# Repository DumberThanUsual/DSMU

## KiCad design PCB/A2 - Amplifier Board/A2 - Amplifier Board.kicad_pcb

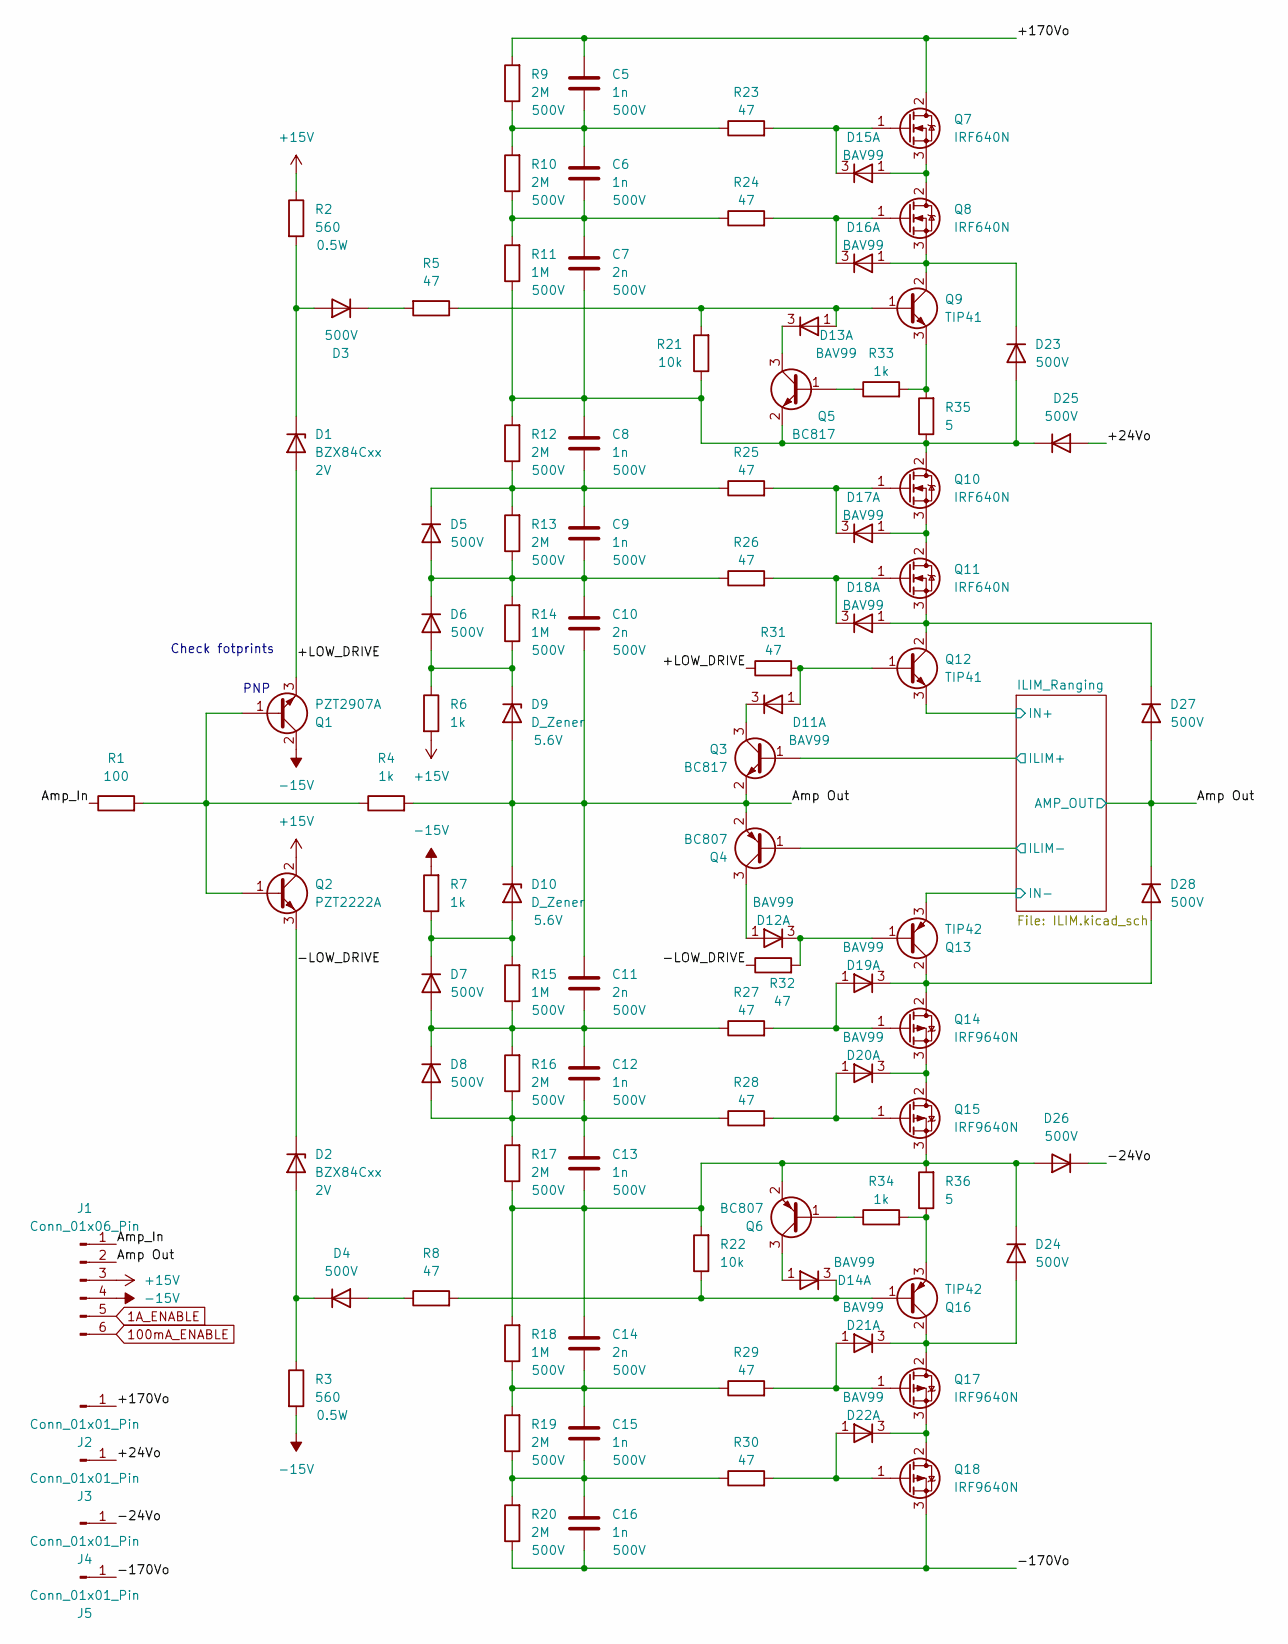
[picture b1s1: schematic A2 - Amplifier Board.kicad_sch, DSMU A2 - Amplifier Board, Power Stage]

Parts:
C5, C6, C8, C9, C12, C13, C15, C16: 1n; C_1206_3216Metric; Voltage Rating 500V
C7, C10, C11, C14: 2n; C_1206_3216Metric; Voltage Rating 500V
D1, D2: BZX84Cxx; SOT-23; Zener Voltage 2V
D3, D4, D5, D6, D7, D8, D23, D24, D25, D26, D27, D28: STTH1R06A; D_SMA; Volatage Rating 500V
D9, D10: D_Zener; D_SOD-123; Zener Voltage 5.6V
D11, D12, D13, D14, D15, D16, D17, D18, D19, D20, D21, D22: BAV99; SOT-23-3
J1: Conn_01x06_Pin; PinHeader_1x06_P2.54mm_Vertical
J2, J3, J4, J5: Conn_01x01_Pin; PinHeader_1x01_P2.54mm_Vertical
Q1: PZT2907A; SOT-223-3_TabPin2
Q2: PZT2222A; SOT-223-3_TabPin2
Q3, Q5: BC817; SOT-23
Q4, Q6: BC807; SOT-23
Q7, Q8, Q10, Q11: IRF640N; TO-220-3_Vertical
Q9, Q12: TIP41; TO-220-3_Vertical
Q13, Q16: TIP42; TO-220-3_Vertical
Q14, Q15, Q17, Q18: IRF9640N; TO-220-3_Vertical
R1: 100; R_0603_1608Metric
R2, R3: 560; R_1206_3216Metric; Power Rating 0.5W
R4, R6, R7, R33, R34: 1k; R_0603_1608Metric
R5, R8, R23, R24, R25, R26, R27, R28, R29, R30, R31, R32: 47; R_0603_1608Metric
R9, R10, R12, R13, R16, R17, R19, R20: 2M; R_1206_3216Metric; Voltage Rating 500V
R11, R14, R15, R18: 1M; R_1206_3216Metric; Voltage Rating 500V
R21, R22: 10k; R_0603_1608Metric
R35, R36: 5; R_0603_1608Metric

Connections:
1A_ENABLE: J1.5; also elsewhere on the board
100mA_ENABLE: J1.6; also elsewhere on the board
/+24Vo: D25.2 (A), J3.1
/+170Vo: C5.1, J2.1, Q7.2 (D), R9.2
/+LOW_DRIVE: D1.1 (A), Q1.3 (E), R31.1
/-24Vo: D26.1 (K), J4.1
/-170Vo: C16.2, J5.1, Q18.3 (S), R20.1
/-LOW_DRIVE: D2.3 (K), Q2.3 (E), R32.1
/Amp Out: C10.2, C11.1, D9.2 (A), D10.1 (K), D27.2 (A), D28.1 (K), J1.2, Q3.2 (E), Q4.2 (E), R4.2; also elsewhere on the board
/Amp_In: J1.1, R1.1
/ILIM_Ranging/ILIM+: Q3.1 (B); also elsewhere on the board
/ILIM_Ranging/ILIM-: Q4.1 (B); also elsewhere on the board
/ILIM_Ranging/IN+: Q12.3 (E); also elsewhere on the board
/ILIM_Ranging/IN-: Q13.3 (E); also elsewhere on the board
unnamed: C5.2, C6.1, R9.1, R10.2, R23.1
unnamed: C6.2, C7.1, R10.1, R11.2, R24.1
unnamed: C14.2, C15.1, R18.1, R19.2, R29.1
unnamed: C15.2, C16.1, R19.1, R20.2, R30.1
unnamed: D1.3 (K), D3.2 (A), R2.2
unnamed: D2.1 (A), D4.1 (K), R3.1
unnamed: D3.1 (K), R5.2
unnamed: D4.2 (A), R8.1
unnamed: C9.2, C10.1, D5.2 (A), D6.1 (K), R13.1, R14.2, R26.1
unnamed: C8.2, C9.1, D5.1 (K), R12.1, R13.2, R25.1
unnamed: D6.2 (A), D9.1 (K), R6.1, R14.1
unnamed: C11.2, C12.1, D7.2 (A), D8.1 (K), R15.1, R16.2, R27.1
unnamed: C12.2, C13.1, D8.2 (A), R16.1, R17.2, R28.1
unnamed: D7.1 (K), D10.2 (A), R7.1, R15.2
unnamed: D11.1 (A), Q12.1 (B), R31.2
unnamed: D11.3 (K), Q3.3 (C)
unnamed: D12.1 (A), Q4.3 (C)
unnamed: D12.3 (K), Q13.1 (B), R32.2
unnamed: D13.1 (A), Q9.1 (B), R5.1, R21.2
unnamed: D13.3 (K), Q5.3 (C)
unnamed: D14.1 (A), Q6.3 (C)
unnamed: D14.3 (K), Q16.1 (B), R8.2, R22.1
unnamed: D15.1 (A), Q7.3 (S), Q8.2 (D)
unnamed: D15.3 (K), Q7.1 (G), R23.2
unnamed: D16.1 (A), D23.1 (K), Q8.3 (S), Q9.2 (C)
unnamed: D16.3 (K), Q8.1 (G), R24.2
unnamed: D17.1 (A), Q10.3 (S), Q11.2 (D)
unnamed: D17.3 (K), Q10.1 (G), R25.2
unnamed: D18.1 (A), D27.1 (K), Q11.3 (S), Q12.2 (C)
unnamed: D18.3 (K), Q11.1 (G), R26.2
unnamed: D19.1 (A), Q14.1 (G), R27.2
unnamed: D19.3 (K), D28.2 (A), Q13.2 (C), Q14.2 (D)
unnamed: D20.1 (A), Q15.1 (G), R28.2
unnamed: D20.3 (K), Q14.3 (S), Q15.2 (D)
unnamed: D21.1 (A), Q17.1 (G), R29.2
unnamed: D21.3 (K), D24.2 (A), Q16.2 (C), Q17.2 (D)
unnamed: D22.1 (A), Q18.1 (G), R30.2
unnamed: D22.3 (K), Q17.3 (S), Q18.2 (D)
unnamed: C7.2, C8.1, D23.2 (A), D25.1 (K), Q5.2 (E), Q10.2 (D), R11.1, R12.2, R21.1, R35.1
unnamed: C13.2, C14.1, D24.1 (K), D26.2 (A), Q6.2 (E), Q15.3 (S), R17.1, R18.2, R22.2, R36.2
unnamed: Q5.1 (B), R33.1
unnamed: Q6.1 (B), R34.1
unnamed: Q9.3 (E), R33.2, R35.2
unnamed: Q16.3 (E), R34.2, R36.1

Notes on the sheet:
PNP
Check fotprints

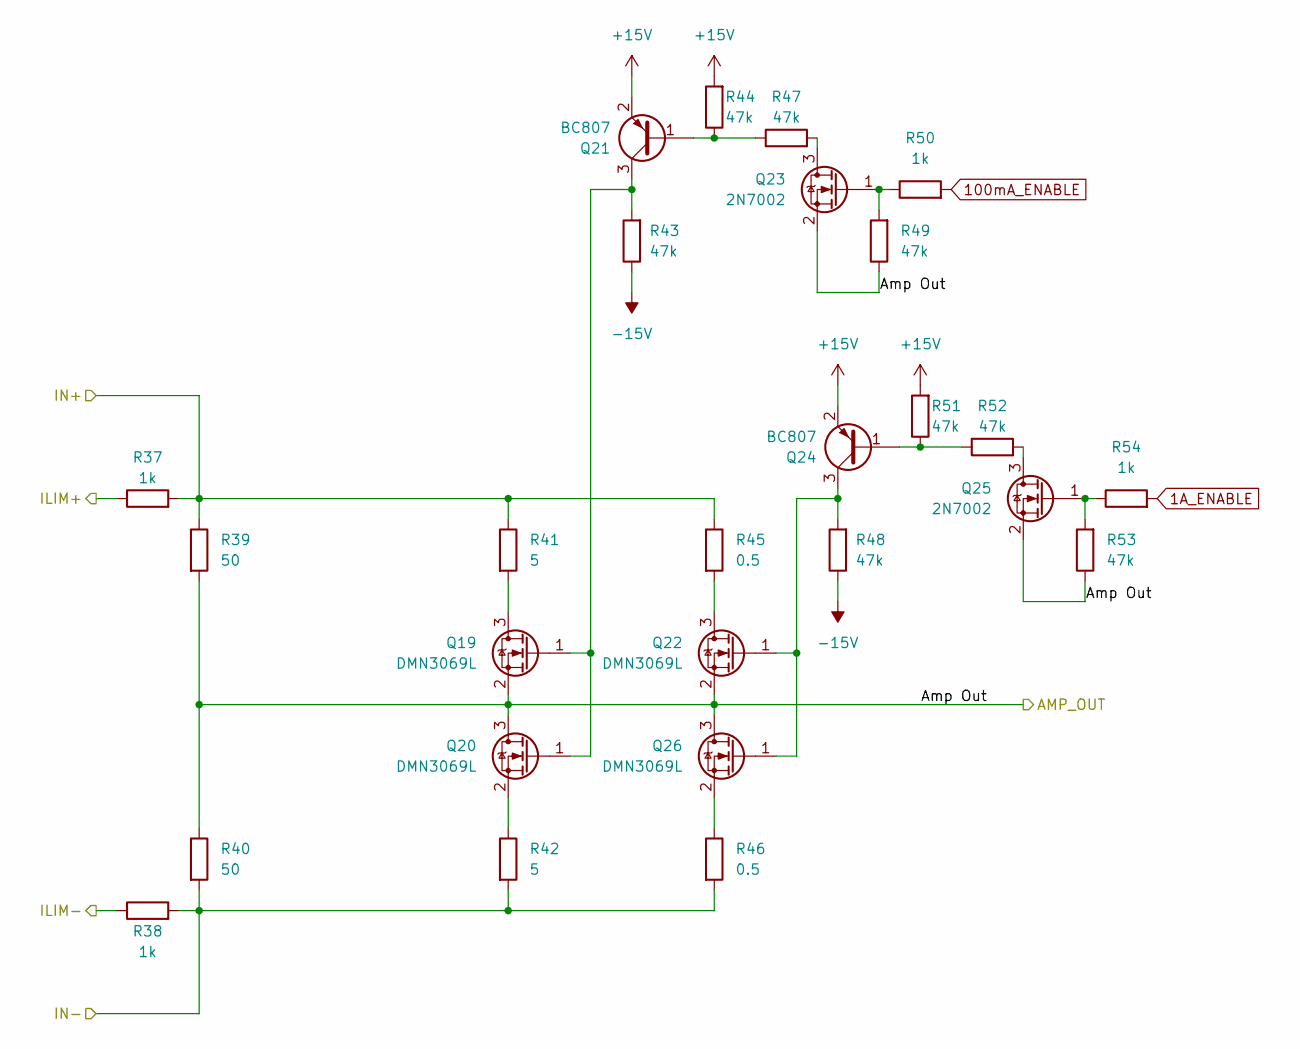
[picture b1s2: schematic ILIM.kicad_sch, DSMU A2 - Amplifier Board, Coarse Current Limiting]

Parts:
Q19, Q20, Q22, Q26: DMN3069L; SOT-23
Q21, Q24: BC807; SOT-23
Q23, Q25: 2N7002; SOT-23
R37, R38, R50, R54: 1k; R_0603_1608Metric
R39, R40: 50; R_0603_1608Metric
R41, R42: 5; R_0603_1608Metric
R43, R44, R47, R48, R49, R51, R52, R53: 47k; R_0603_1608Metric
R45, R46: 0.5; R_0603_1608Metric

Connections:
1A_ENABLE: R54.2; also elsewhere on the board
100mA_ENABLE: R50.2; also elsewhere on the board
/Amp Out: Q19.2 (S), Q20.3 (D), Q22.2 (S), Q23.2 (S), Q25.2 (S), Q26.3 (D), R39.2, R40.1, R49.1, R53.1; also elsewhere on the board
/ILIM_Ranging/ILIM+: R37.1; also elsewhere on the board
/ILIM_Ranging/ILIM-: R38.1; also elsewhere on the board
/ILIM_Ranging/IN+: R37.2, R39.1, R41.1, R45.1; also elsewhere on the board
/ILIM_Ranging/IN-: R38.2, R40.2, R42.2, R46.2; also elsewhere on the board
unnamed: Q19.3 (D), R41.2
unnamed: Q19.1 (G), Q20.1 (G), Q21.3 (C), R43.2
unnamed: Q20.2 (S), R42.1
unnamed: Q21.1 (B), R44.1, R47.1
unnamed: Q22.3 (D), R45.2
unnamed: Q22.1 (G), Q24.3 (C), Q26.1 (G), R48.2
unnamed: Q23.3 (D), R47.2
unnamed: Q23.1 (G), R49.2, R50.1
unnamed: Q24.1 (B), R51.1, R52.1
unnamed: Q25.3 (D), R52.2
unnamed: Q25.1 (G), R53.2, R54.1
unnamed: Q26.2 (S), R46.1

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
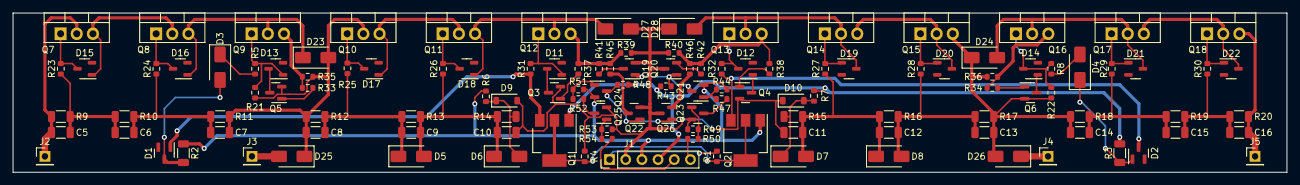
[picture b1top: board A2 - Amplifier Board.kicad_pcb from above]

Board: 2 copper layers, 200.0 x 25.0 mm, 125 parts (0 on the bottom side), 73 nets.

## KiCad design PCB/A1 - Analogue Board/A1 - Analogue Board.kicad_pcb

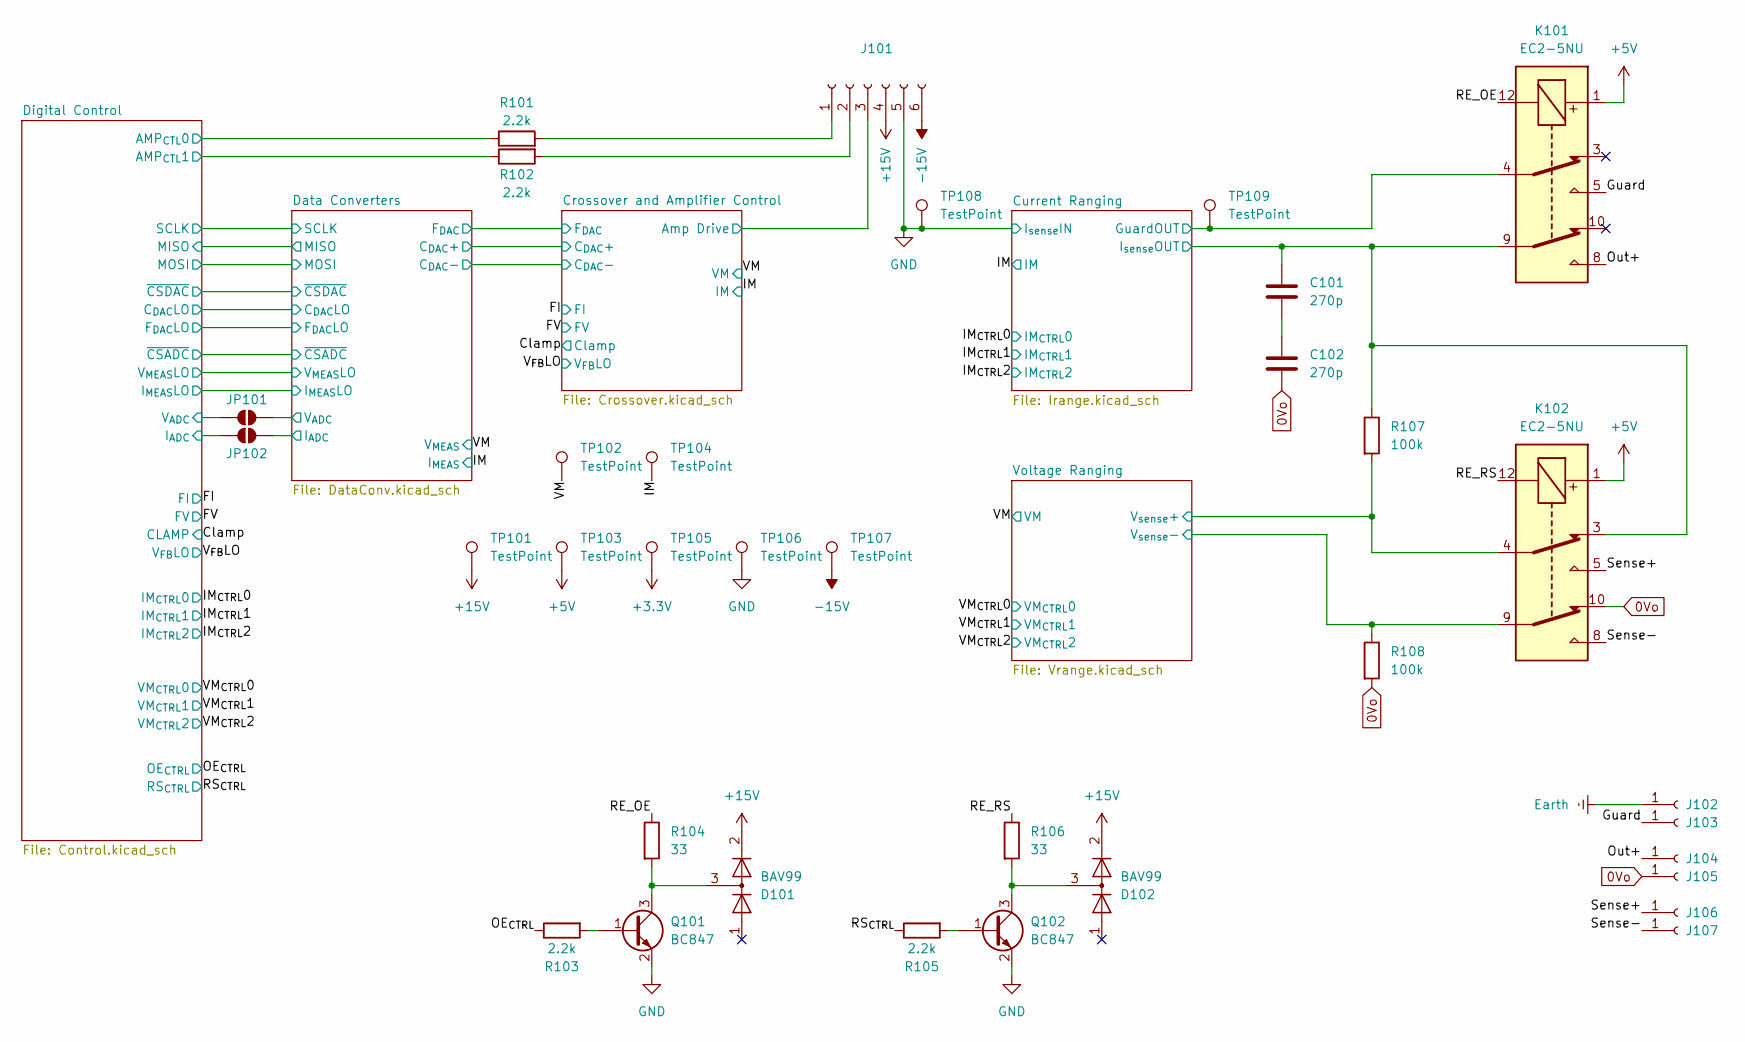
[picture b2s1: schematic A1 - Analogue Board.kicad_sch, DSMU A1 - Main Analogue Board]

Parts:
C101, C102: 270p; C_0805_2012Metric
D101, D102: BAV99; SOT-23
J101: Conn_01x06_Socket; PinHeader_1x06_P2.54mm_Vertical
J102, J103, J104, J105, J106, J107: Conn_01x01_Socket; PinHeader_1x01_P2.54mm_Vertical
JP101, JP102: SolderJumper_2_Open; SolderJumper-2_P1.3mm_Open_RoundedPad1.0x1.5mm
K101, K102: EC2-5NU; Relay_DPDT_Kemet_EC2
Q101, Q102: BC847; SOT-23
R101, R102, R103, R105: 2.2k; R_0603_1608Metric
R104, R106: 33; R_0603_1608Metric
R107, R108: 100k; R_0603_1608Metric
TP101, TP102, TP103, TP104, TP105, TP106, TP107, TP108, TP109: TestPoint; Pin_D1.0mm_L10.0mm

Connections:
0Vo: C102.1, J105.1, K102.10, R108.2; also elsewhere on the board
+3.3V: TP105.1; also elsewhere on the board
+5V: K101.1, K102.1, TP103.1; also elsewhere on the board
+15V: D101.2 (A), D102.2 (A), J101.4, TP101.1; also elsewhere on the board
-15V: J101.6, TP107.1; also elsewhere on the board
/Crossover and Amplifier Control/Amp Drive: J101.3; also elsewhere on the board
/Current Ranging/GuardOUT: K101.4, TP109.1; also elsewhere on the board
/Current Ranging/I_{sense}OUT: C101.2, K101.9, K102.3, R107.1; also elsewhere on the board
/Data Converters/I_{ADC}: JP102.1 (A); also elsewhere on the board
/Data Converters/V_{ADC}: JP101.1 (A); also elsewhere on the board
/Digital Control/AMP_{CTL}0: R101.1; also elsewhere on the board
/Digital Control/AMP_{CTL}1: R102.1; also elsewhere on the board
/Digital Control/I_{ADC}: JP102.2 (B); also elsewhere on the board
/Digital Control/V_{ADC}: JP101.2 (B); also elsewhere on the board
/Guard: J103.1, K101.5
/IM: TP104.1; also elsewhere on the board
/OE_{CTRL}: R103.1; also elsewhere on the board
/Out+: J104.1, K101.8
/RE_OE: K101.12, R104.1
/RE_RS: K102.12, R106.1
/RS_{CTRL}: R105.1; also elsewhere on the board
/Sense+: J106.1, K102.5
/Sense-: J107.1, K102.8
/VM: TP102.1; also elsewhere on the board
/Voltage Ranging/V_{sense}+: K102.4, R107.2; also elsewhere on the board
/Voltage Ranging/V_{sense}-: K102.9, R108.1; also elsewhere on the board
Earth: J102.1
GND: J101.5, Q101.2 (E), Q102.2 (E), TP106.1, TP108.1; also elsewhere on the board
unnamed: C101.1, C102.2
unnamed: J101.1, R101.2
unnamed: J101.2, R102.2
unnamed: Q101.1 (B), R103.2
unnamed: D101.3 (K), Q101.3 (C), R104.2
unnamed: Q102.1 (B), R105.2
unnamed: D102.3 (K), Q102.3 (C), R106.2

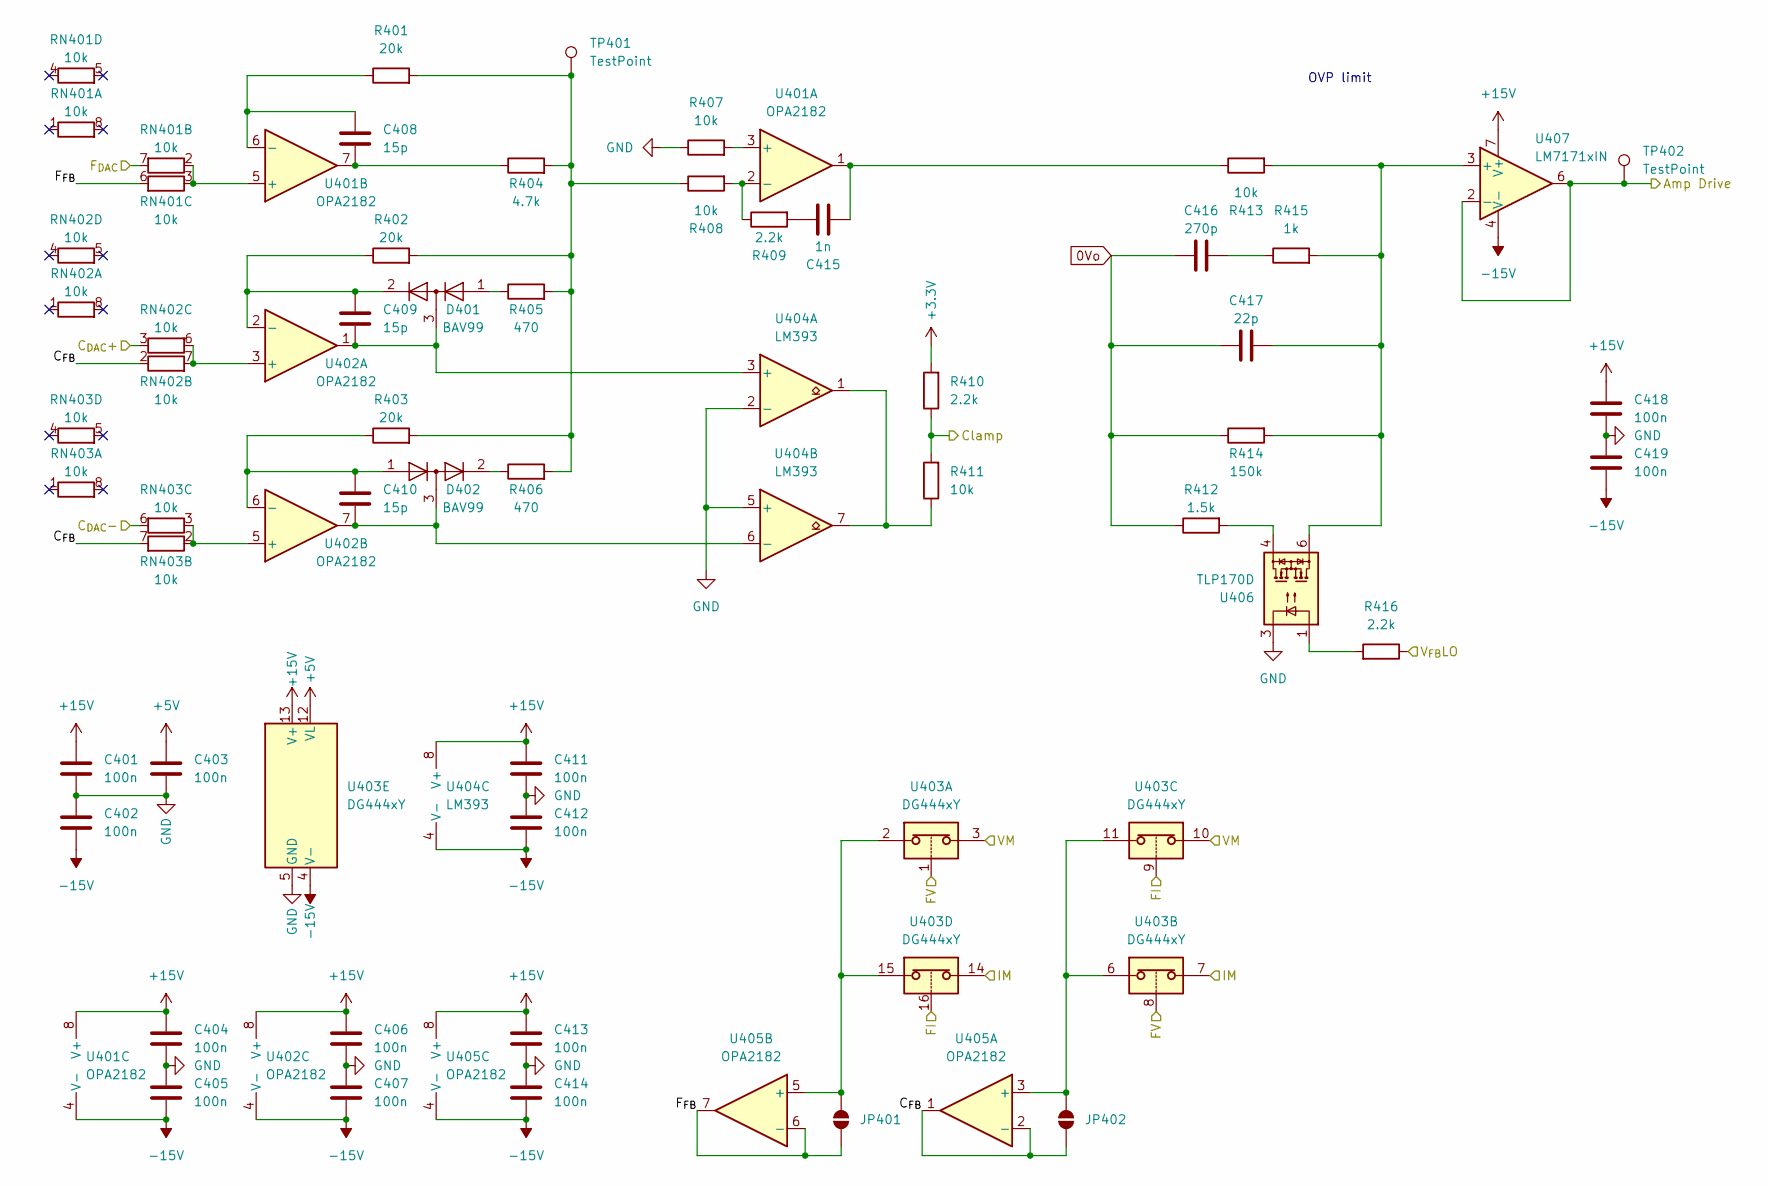
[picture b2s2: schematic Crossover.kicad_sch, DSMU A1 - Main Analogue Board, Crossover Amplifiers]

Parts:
C401, C402, C403, C404, C405, C406, C407, C411, C412, C413, C414, C418, C419: 100n; C_0603_1608Metric
C408, C409, C410: 15p; C_0603_1608Metric
C415: 1n; C_0603_1608Metric
C416: 270p; C_0805_2012Metric
C417: 22p; C_1206_3216Metric
D401, D402: BAV99; SOT-23
JP401, JP402: SolderJumper_2_Open; SolderJumper-2_P1.3mm_Open_RoundedPad1.0x1.5mm
R401, R402, R403: 20k; R_0603_1608Metric
R404: 4.7k; R_0603_1608Metric
R405, R406: 470; R_0603_1608Metric
R407, R408, R411: 10k; R_0603_1608Metric
R409, R410, R416: 2.2k; R_0603_1608Metric
R412: 1.5k; R_1206_3216Metric
R413: 10k; R_0805_2012Metric
R414: 150k; R_1206_3216Metric
R415: 1k; R_1206_3216Metric
RN401, RN402, RN403: 10k; R_Array_Concave_4x0603
TP401, TP402: TestPoint; Pin_D1.0mm_L10.0mm
U401, U402, U405: OPA2182; SOIC-8_3.9x4.9mm_P1.27mm
U403: DG444xY; SOIC-16_3.9x9.9mm_P1.27mm
U404: LM393; SOIC-8_3.9x4.9mm_P1.27mm
U406: TLP170D; MFSOP6-4_4.4x3.6mm_P1.27mm
U407: LM7171xIN; DIP-8_W7.62mm

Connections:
0Vo: C416.1, C417.1, R412.1, R414.1; also elsewhere on the board
+3.3V: R410.2; also elsewhere on the board
+5V: C403.1, U403.12 (VL); also elsewhere on the board
+15V: C401.1, C404.1, C406.1, C411.1, C413.1, C418.1, U401.8 (V+), U402.8 (V+), U403.13 (V+), U404.8 (V+), U405.8 (V+), U407.7 (V+); also elsewhere on the board
-15V: C402.2, C405.2, C407.2, C412.2, C414.2, C419.2, U401.4 (V-), U402.4 (V-), U403.4 (V-), U404.4 (V-), U405.4 (V-), U407.4 (V-); also elsewhere on the board
/Clamp: R410.1, R411.2; also elsewhere on the board
/Crossover and Amplifier Control/Amp Drive: TP402.1, U407.2 (-), U407.6; also elsewhere on the board
/Crossover and Amplifier Control/C_{DAC}+: RN402.3 (R3.1); also elsewhere on the board
/Crossover and Amplifier Control/C_{DAC}-: RN403.6 (R3.2); also elsewhere on the board
/Crossover and Amplifier Control/C_{FB}: JP402.1 (A), RN402.2 (R2.1), RN403.7 (R2.2), U405.1, U405.2 (-)
/Crossover and Amplifier Control/F_{DAC}: RN401.7 (R2.2); also elsewhere on the board
/Crossover and Amplifier Control/F_{FB}: JP401.1 (A), RN401.6 (R3.2), U405.6 (-), U405.7
/FI: U403.9, U403.16; also elsewhere on the board
/FV: U403.1, U403.8; also elsewhere on the board
/IM: U403.7, U403.14; also elsewhere on the board
/VM: U403.3, U403.10; also elsewhere on the board
/V_{FB}LO: R416.1; also elsewhere on the board
GND: C401.2, C402.1, C403.2, C404.2, C405.1, C406.2, C407.1, C411.2, C412.1, C413.2, C414.1, C418.2, C419.1, R407.1, U403.5 (GND), U404.2 (-), U404.5 (+), U406.3; also elsewhere on the board
unnamed: C408.2, R404.1, U401.7
unnamed: C415.1, R409.2
unnamed: C415.2, R413.1, U401.1
unnamed: C416.2, R415.1
unnamed: C409.1, D401.2 (A), R402.1, U402.2 (-)
unnamed: D401.1 (K), R405.1
unnamed: D402.2 (A), R406.1
unnamed: JP401.2 (B), U403.2, U403.15, U405.5 (+)
unnamed: JP402.2 (B), U403.6, U403.11, U405.3 (+)
unnamed: R401.2, R402.2, R403.2, R404.2, R405.2, R406.2, R408.1, TP401.1
unnamed: R411.1, U404.1, U404.7
unnamed: R412.2, U406.4
unnamed: R416.2, U406.1
unnamed: RN401.2 (R2.1), RN401.3 (R3.1), U401.5 (+)
unnamed: RN402.6 (R3.2), RN402.7 (R2.2), U402.3 (+)
unnamed: RN403.2 (R2.1), RN403.3 (R3.1), U402.5 (+)
unnamed: R407.2, U401.3 (+)
unnamed: R408.2, R409.1, U401.2 (-)
unnamed: C408.1, R401.1, U401.6 (-)
unnamed: C410.1, D402.1 (K), R403.1, U402.6 (-)
unnamed: C409.2, D401.3 (K), U402.1, U404.3 (+)
unnamed: C410.2, D402.3 (K), U402.7, U404.6 (-)
unnamed: C417.2, R413.2, R414.2, R415.2, U406.6, U407.3 (+)

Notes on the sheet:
OVP limit

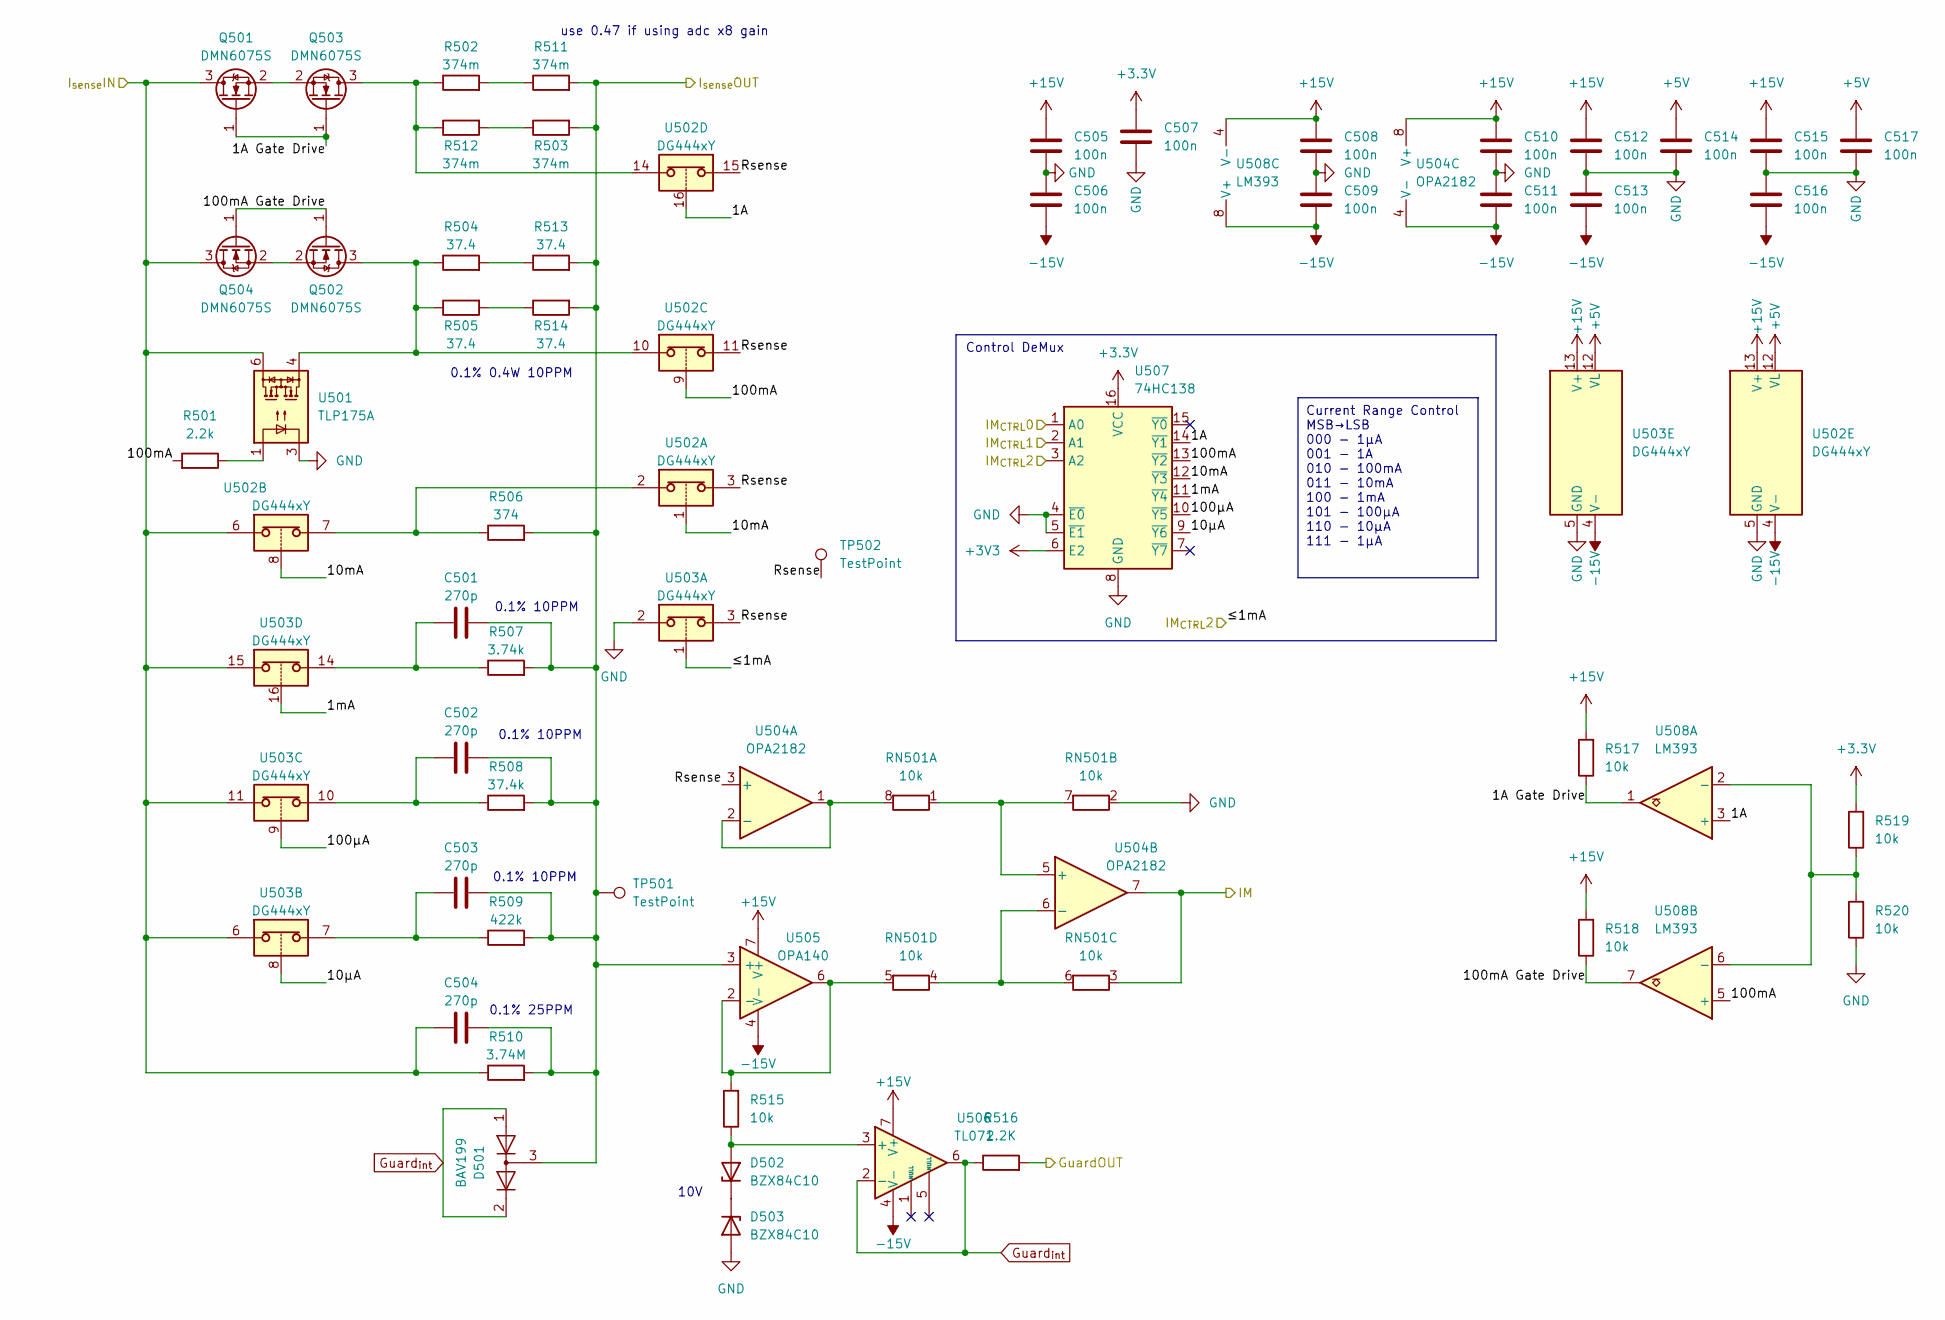
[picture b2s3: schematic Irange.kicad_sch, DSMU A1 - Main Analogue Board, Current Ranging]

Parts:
C501, C502, C503, C504: 270p; C_0805_2012Metric
C505, C506, C507, C508, C509, C510, C511, C512, C513, C514, C515, C516, C517: 100n; C_0603_1608Metric
D501: BAV199; SOT-23
D502, D503: BZX84C10; SOT-23
Q501, Q502, Q503, Q504: DMN6075S; SOT-23
R501: 2.2k; R_0603_1608Metric
R502, R503, R511, R512: 374m; R_1206_3216Metric
R504, R505, R513, R514: 37.4; R_1206_3216Metric
R506: 374; R_0805_2012Metric
R507: 3.74k; R_0805_2012Metric
R508: 37.4k; R_0805_2012Metric
R509: 422k; R_1206_3216Metric
R510: 3.74M; R_1206_3216Metric
R515, R517, R518, R519, R520: 10k; R_0603_1608Metric
R516: 2.2K; R_0603_1608Metric
RN501: 10k; R_Array_Convex_4x0612
TP501, TP502: TestPoint; Pin_D1.0mm_L10.0mm
U501: TLP175A; MFSOP6-4_4.4x3.6mm_P1.27mm
U502, U503: DG444xY; SOIC-16_3.9x9.9mm_P1.27mm
U504: OPA2182; SOIC-8_3.9x4.9mm_P1.27mm
U505: OPA140; SOIC-8_3.9x4.9mm_P1.27mm
U506: TL071; SOIC-8_3.9x4.9mm_P1.27mm
U507: 74HC138; SOIC-16_3.9x9.9mm_P1.27mm
U508: LM393; SOIC-8_3.9x4.9mm_P1.27mm

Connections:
+3.3V: C507.1, R519.2, U507.16 (VCC); also elsewhere on the board
+3V3: U507.6 (E2); also elsewhere on the board
+5V: C514.1, C517.1, U502.12 (VL), U503.12 (VL); also elsewhere on the board
+15V: C505.1, C508.1, C510.1, C512.1, C515.1, R517.2, R518.2, U502.13 (V+), U503.13 (V+), U504.8 (V+), U505.7 (V+), U506.7 (V+), U508.4 (V-); also elsewhere on the board
-15V: C506.2, C509.2, C511.2, C513.2, C516.2, U502.4 (V-), U503.4 (V-), U504.4 (V-), U505.4 (V-), U506.4 (V-), U508.8 (V+); also elsewhere on the board
/Current Ranging/1A: U502.16, U507.14 (~Y1), U508.3 (+)
/Current Ranging/1A Gate Drive: Q501.1 (G), Q503.1 (G), R517.1, U508.1
/Current Ranging/1mA: U503.16, U507.11 (~Y4)
/Current Ranging/10mA: U502.1, U502.8, U507.12 (~Y3)
/Current Ranging/10µA: U503.8, U507.9 (~Y6)
/Current Ranging/100mA: R501.2, U502.9, U507.13 (~Y2), U508.5 (+)
/Current Ranging/100mA Gate Drive: Q502.1 (G), Q504.1 (G), R518.1, U508.7
/Current Ranging/100µA: U503.9, U507.10 (~Y5)
/Current Ranging/GuardOUT: R516.2; also elsewhere on the board
/Current Ranging/I_{sense}OUT: C501.2, C502.2, C503.2, C504.2, D501.3 (K), R506.2, R507.2, R508.2, R509.2, R510.2, R511.2, R512.2, R513.2, R514.2, TP501.1, U505.3 (+); also elsewhere on the board
/Current Ranging/Rsense: TP502.1, U502.3, U502.11, U502.15, U503.3, U504.3 (+)
/IM: RN501.3 (R3.1), U504.7; also elsewhere on the board
/IM_{CTRL}0: U507.1 (A0); also elsewhere on the board
/IM_{CTRL}1: U507.2 (A1); also elsewhere on the board
/IM_{CTRL}2: U503.1, U507.3 (A2); also elsewhere on the board
GND: C504.1, C505.2, C506.1, C507.2, C508.2, C509.1, C510.2, C511.1, C512.2, C513.1, C514.2, C515.2, C516.1, C517.2, D503.1 (A), Q501.3 (D), Q502.3 (D), R510.1, R520.1, RN501.2 (R2.1), U501.3, U501.6, U502.5 (GND), U502.6, U503.2, U503.5 (GND), U503.6, U503.11, U503.15, U507.4 (~E0), U507.5 (~E1), U507.8 (GND); also elsewhere on the board
Guard_{int}: D501.1 (K), D501.2 (A), R516.1, U506.2 (-), U506.6
unnamed: C501.1, R507.1, U503.14
unnamed: C502.1, R508.1, U503.10
unnamed: C503.1, R509.1, U503.7
unnamed: D502.1 (A), R515.1, U506.3 (+)
unnamed: D502.3 (K), D503.3 (K)
unnamed: Q501.2 (S), Q503.2 (S)
unnamed: Q502.2 (S), Q504.2 (S)
unnamed: Q503.3 (D), R502.1, R503.1, U502.14
unnamed: Q504.3 (D), R504.1, R505.1, U501.4, U502.10
unnamed: R501.1, U501.1
unnamed: R502.2, R511.1
unnamed: R503.2, R512.1
unnamed: R504.2, R513.1
unnamed: R505.2, R514.1
unnamed: R506.1, U502.2, U502.7
unnamed: RN501.1 (R1.1), RN501.7 (R2.2), U504.5 (+)
unnamed: RN501.8 (R1.2), U504.1, U504.2 (-)
unnamed: RN501.4 (R4.1), RN501.6 (R3.2), U504.6 (-)
unnamed: R515.2, RN501.5 (R4.2), U505.2 (-), U505.6
unnamed: R519.1, R520.2, U508.2 (-), U508.6 (-)

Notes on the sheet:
Current Range Control MSB→LSB 000 - 1µA 001 - 1A 010 - 100mA 011 - 10mA 100 - 1mA 101 - 100µA 110 - 10µA 111 - 1µA
use 0.47 if using adc x8 gain
0.1% 0.4W 10PPM
Control DeMux
0.1% 10PPM
10V
0.1% 25PPM
